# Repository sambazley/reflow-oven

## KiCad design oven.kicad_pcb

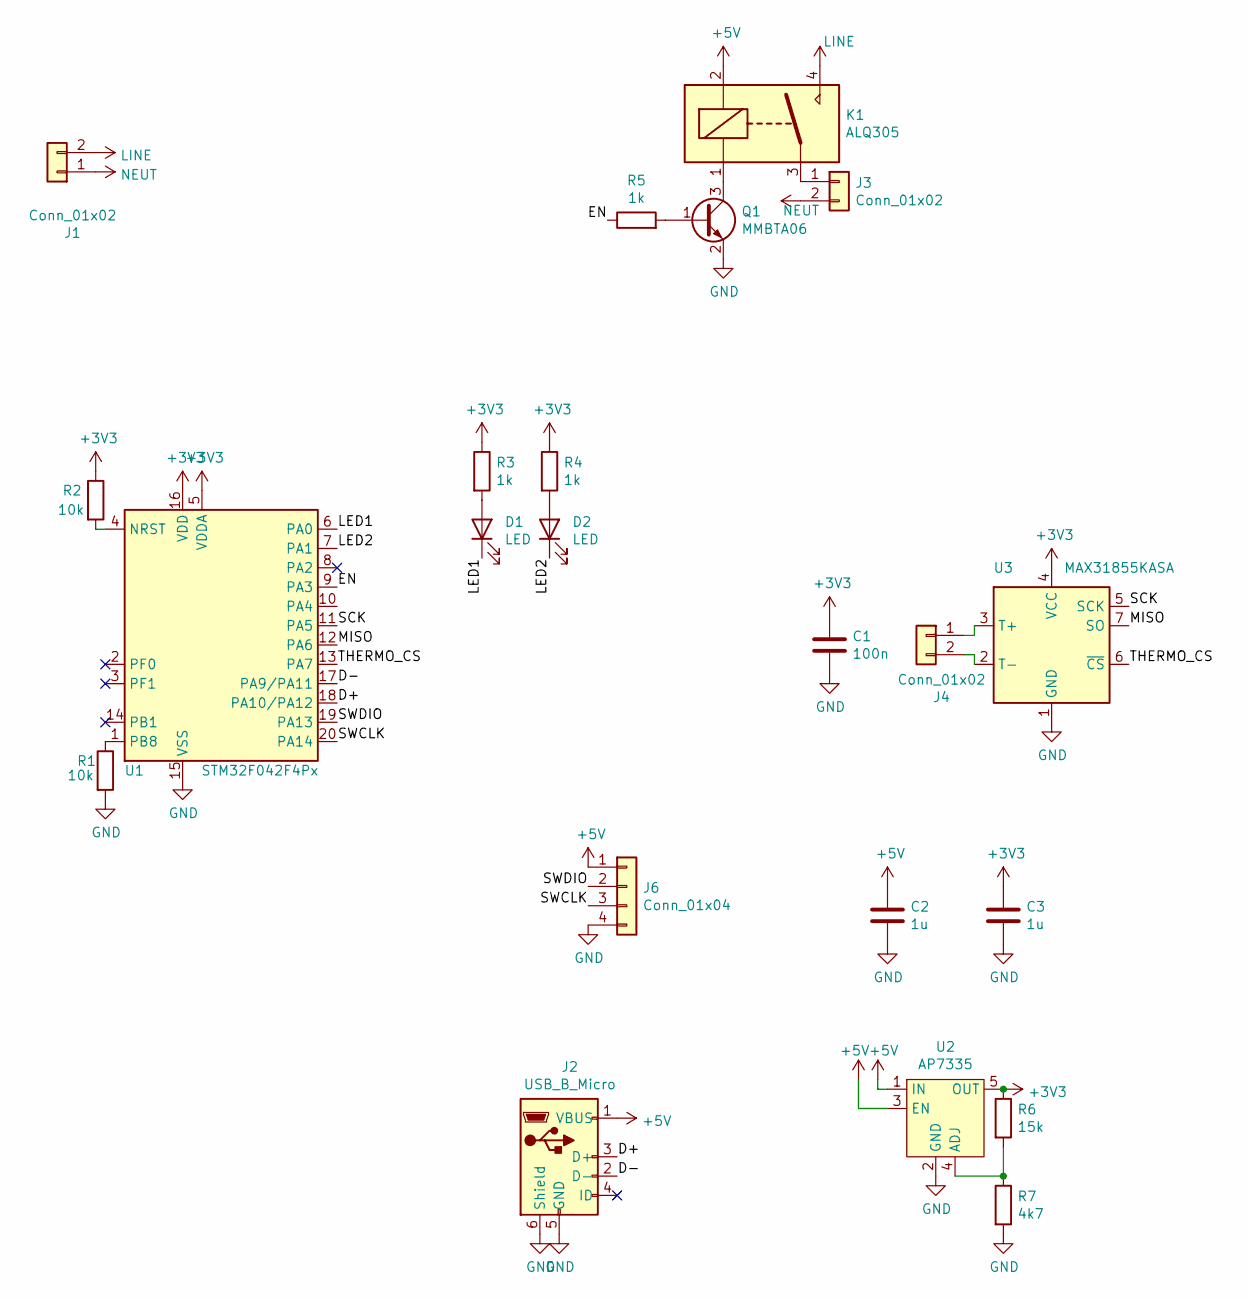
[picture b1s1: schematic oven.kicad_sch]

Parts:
C1: 100n; C_0805_2012Metric
C2, C3: 1u; C_0805_2012Metric
D1, D2: LED; LED_0805_2012Metric
J1, J3: Conn_01x02; JST_VH_B2P3-VH_1x02_P7.92mm_Vertical
J2: USB_B_Micro; USB_Micro-B_Amphenol_10118194-0001LF
J4: Conn_01x02; JST_VH_B2P-VH_1x02_P3.96mm_Vertical
J6: Conn_01x04; PinHeader_1x04_P2.54mm_Vertical
K1: ALQ305
Q1: MMBTA06; SOT-23
R1, R2: 10k; R_0805_2012Metric
R3, R4, R5: 1k; R_0805_2012Metric
R6: 15k; R_0805_2012Metric
R7: 4k7; R_0805_2012Metric
U1: STM32F042F4Px; TSSOP-20_4.4x6.5mm_P0.65mm
U2: AP7335; SOT-23-5
U3: MAX31855KASA; SOIC-8_3.9x4.9mm_P1.27mm

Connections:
+3V3: C1.1, C3.1, R2.1, R3.1, R4.1, R6.1, U1.5 (VDDA), U1.16 (VDD), U2.5 (OUT), U3.4 (VCC)
+5V: C2.1, J2.1 (VBUS), J6.1, K1.2, U2.1 (IN), U2.3 (EN)
/D+: J2.3 (D+), U1.18 (PA10/PA12)
/D-: J2.2 (D-), U1.17 (PA9/PA11)
/EN: R5.1, U1.9 (PA3)
/LED1: D1.1 (K), U1.6 (PA0)
/LED2: D2.1 (K), U1.7 (PA1)
/MISO: U1.12 (PA6), U3.7 (SO)
/SCK: U1.11 (PA5), U3.5 (SCK)
/SWCLK: J6.3, U1.20 (PA14)
/SWDIO: J6.2, U1.19 (PA13)
/THERMO_CS: U1.13 (PA7), U3.6 (~CS~)
GND: C1.2, C2.2, C3.2, J2.5 (GND), J2.6 (Shield), J6.4, Q1.2 (E), R1.2, R7.2, U1.15 (VSS), U2.2 (GND), U3.1 (GND)
LINE: J1.2, K1.4
NEUT: J1.1, J3.2
unnamed: D1.2 (A), R3.2
unnamed: D2.2 (A), R4.2
unnamed: J3.1, K1.3
unnamed: J4.1, U3.3 (T+)
unnamed: J4.2, U3.2 (T-)
unnamed: K1.1, Q1.3 (C)
unnamed: Q1.1 (B), R5.2
unnamed: R1.1, U1.1 (PB8)
unnamed: R2.2, U1.4 (NRST)
unnamed: R6.2, R7.1, U2.4 (ADJ)

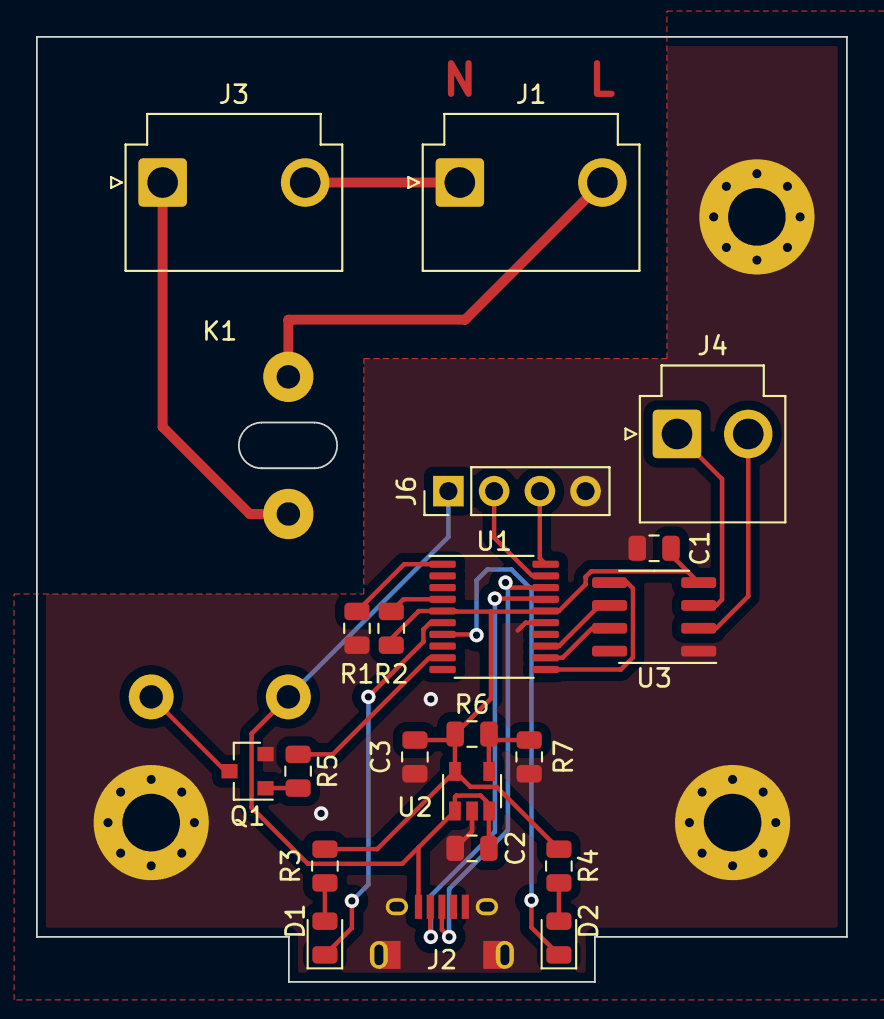
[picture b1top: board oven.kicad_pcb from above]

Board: 2 copper layers, 45.0 x 52.5 mm, 22 parts (0 on the bottom side), 25 nets.

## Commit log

2020-09-24 init
2020-09-24 Add PCB design files
2020-09-24 Add STM32 code
2020-10-13 Use automatic variables in Makefile
2020-11-20 Correct vector table for STM32F0
2021-06-18 Implement USB driver and PID controller
2021-06-19 Add start command
2021-06-19 Disable oven if ovenctl doesn't acknowledge
2021-06-19 Add command to query current temperature
2021-06-20 Flush spi_thermo when querying temperature
